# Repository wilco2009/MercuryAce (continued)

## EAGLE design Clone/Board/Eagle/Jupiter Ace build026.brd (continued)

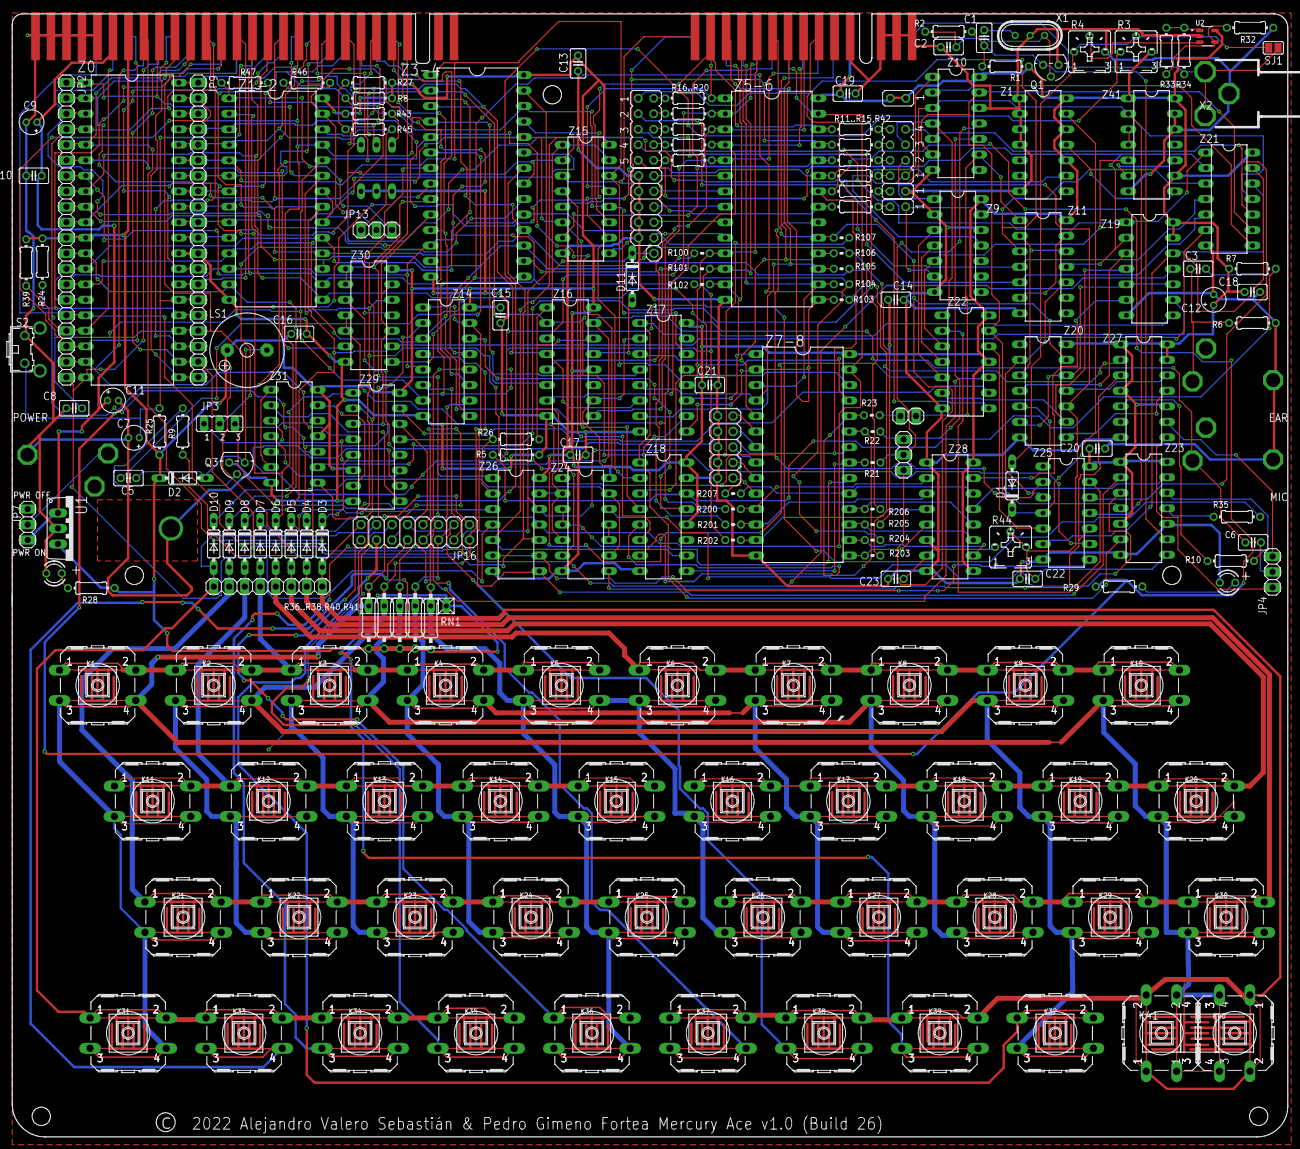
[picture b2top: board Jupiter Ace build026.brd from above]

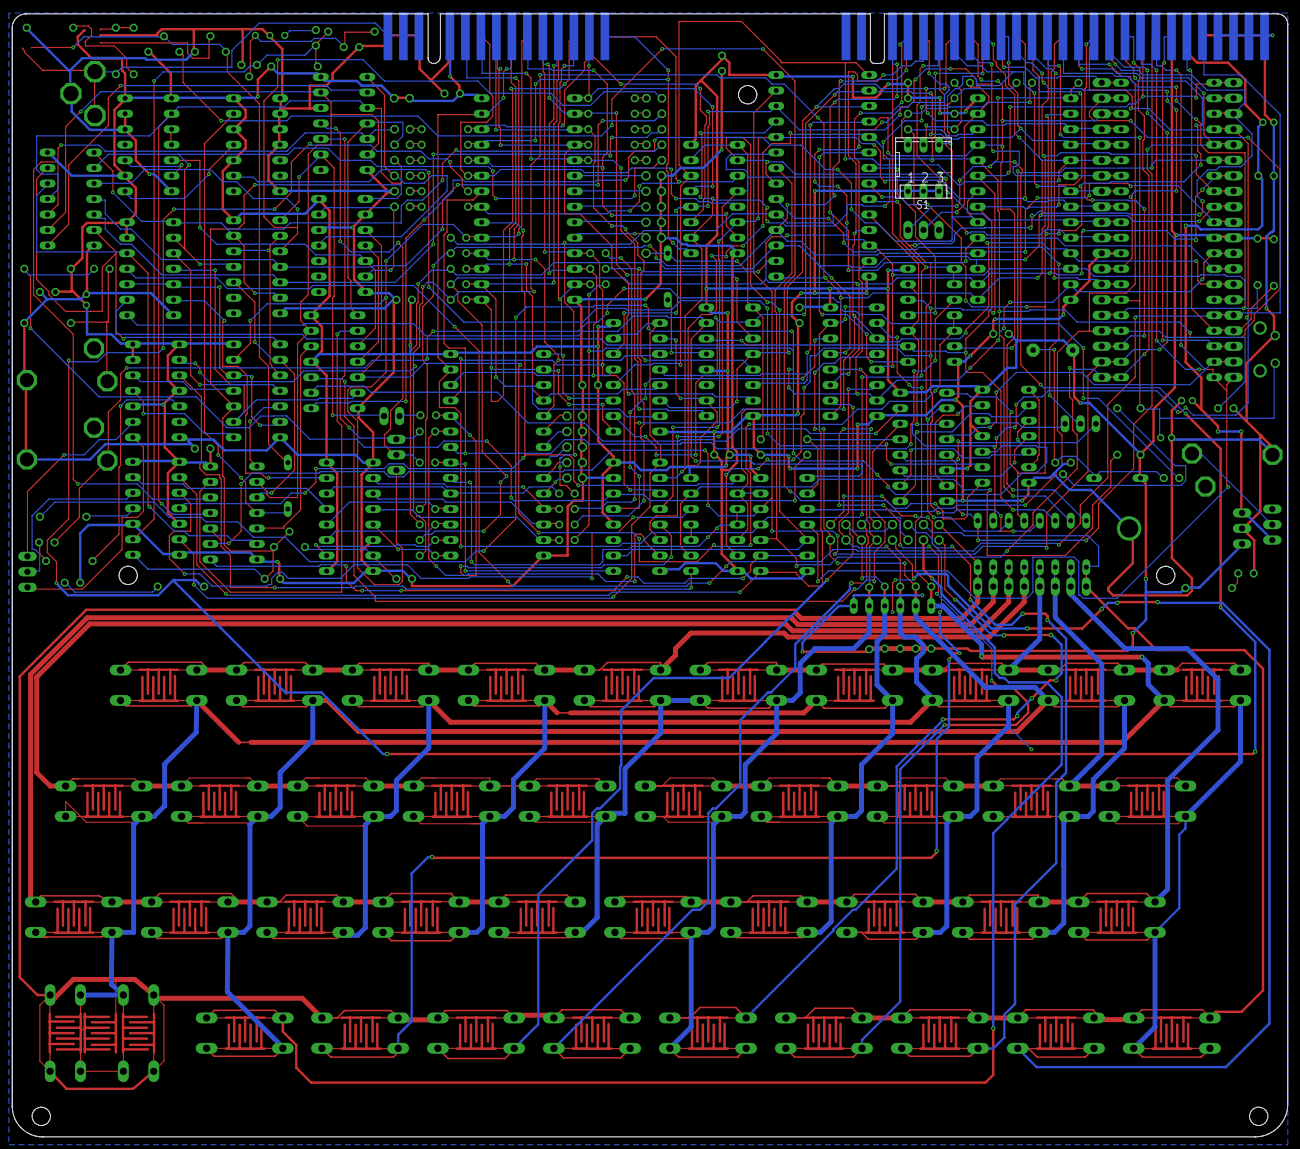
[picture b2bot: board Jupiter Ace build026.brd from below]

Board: 2 copper layers, 209.0 x 184.0 mm, 321 parts (42 on the bottom side), 211 nets.

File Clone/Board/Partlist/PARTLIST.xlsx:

Part | Value | Device | Package | Description | ONLY WITHOUT ACE81 | ONLY WITH ACE81 | ONLY WITH SJ1 OPENED
K1..K41 |  | PUSH BUTTON | B3F-40XXNOHOLE | OMRON
R35 | 300 | R-EU_0204/7 | 0204/7 | RESISTOR,
R26 | 330 | R-EU_0204/7 | 0204/7 | RESISTOR,
R28,R29 | 680 | R-EU_0204/7 | 0204/7 | RESISTOR,
R32 |  | 0204/7 | RESISTOR, | European |  |  | Y
R33 |  | 0204/7 | RESISTOR, | European |  |  | Y
R34 |  | 0204/7 | RESISTOR, | European |  |  | Y
R8,R10,R24,R27,R39,R42 | 10K | R-EU_0204/7 | 0204/7 | RESISTOR,
R5 | 12K | R-EU_0204/7 | 0204/7 | RESISTOR,
R4 | 1K | TRIM_EU-B25P | B25P | POTENTIOMETER |  |  | Y
R1,R6,R11..R23,R100..R107,R200,R207 | 1K | R-EU_0204/7 | 0204/7 | RESISTOR,
R9 | 22K | R-EU_0204/7 | 0204/7 | RESISTOR,
R7 | 33K | R-EU_0204/7 | 0204/7 | RESISTOR,
R2 | 47K | R-EU_0204/7 | 0204/7 | RESISTOR,
R3 | 500R | TRIM_EU-B25P | B25P | POTENTIOMETER
R44 | 1K | TRIM_EU-B25P | B25P | POTENTIOMETER
R30,R31 | 4k7 | R-EU_0204/7 | 0204/7 | RESISTOR, |  | Y
R36..R38,R40,R41 | 4k7 | R-EU_0204/7 | 0204/7 | RESISTOR,
R45..R47 | 4k7 | R-EU_0204/7 | 0204/7 | RESISTOR,
RN1 (instead R36,R37,R38,R40,R41) | 4K7 | RN05 | RN-6 | RESISTOR NETWORK
C4 | DO NOT INSTALL
C10,C13..C21 | 100nF | C-EU025-025X050 | C025-025X050 | CAPACITOR,
C2 | 100pF | C-EU025-025X050 | C025-025X050 | CAPACITOR,
C9 | 100uF | CPOL-EUE1.8-4 | E1,8-4 | POLARIZED
C7,C11,C12 | 1uF | CPOL-EUE1.8-4 | E1,8-4 | POLARIZED
C3 | 2.2uF | C-EU025-025X050 | C025-025X050 | CAPACITOR,
C8 | 2.2nF | C-EU025-025X050 | C025-025X050 | CAPACITOR,
C1 | 30pF | C-EU025-025X050 | C025-025X050 | CAPACITOR,
C22 | 470pF | C-EU025-025X050 | C025-025X050 | CAPACITOR,
C6 | 47nF | C-EU025-025X050 | C025-025X050 | CAPACITOR,
C5 | 47pF | C-EU025-025X050 | C025-025X050 | CAPACITOR,
C23 | 10pF | C-EU025-025X050 | C025-025X050 | CAPACITOR,
D1..D17 | 1N4148DO35-7 | 1N4148DO35-7 | DO35-7 | DIODE | Replace D12..D17 by a 0R resistor
U1 | 7805 | 7805TV | TO220V | Positive
Z1-2 | 27C512 | 27512G | DIL28-6 | MEMORY
Q1 | 2N3904 | 2N3904 | TO92 | NPN
X1 | 6.5MHz | 8M10AHC49T | HC49U | Monolithic
Z0 | Z80 | Z80CPU | DIL40 | Z80
Z1,Z27 | 74LS74N | 74LS74N | DIL14 | Dual
Z3-4,Z5-6,Z7-8 | CY62256LL-PC | SRAM | DIL28-6 | 256Kbit (32KBx8)
Z9,Z10,Z11 | 74LS393N | 74LS393N | DIL14 | Dual
Z14..Z18 | 74367N | 74367N | DIL16 | Hex
Z19,Z30,Z41 | 74LS00N | 74LS00N | DIL14 | Quad
Z20 | 74LS08N | 74LS08N | DIL14 | Quad
Z21,Z22,Z31 | 74LS11N | 74LS11N | DIL14 | Triple
Z23 | 74LS86N | 74LS86N | DIL14 | Quad
Z24,Z25 | 74LS02N | 74LS02N | DIL14 | Quad
Z26 | 74LS32N | 74LS32N | DIL14 | Quad
Z29 | 74LS138N | 74LS138N | DIL16 | 3-line
Z28 | 74LS166N | 74LS166N | DIL16 | 8-bit
Z40 | ATF16V8BP3 | ATF16V8BP3 | DIL20 | High | N | Y
LED1 | POWER | RED | LED3MM | LED
LED2 | ACE81 | BLUE | LED3MM | LED | N | Y
Q3 | BC337 | BC337 | TO92 | NPN
X2 | VIDEO CONN | AV-8.4-5 3 PINES
LS1 | PASSIVE BUZZER 16 ohm | F/QMX | F/QMX | BUZZER
U2 | MAX4390EUK | MAX4390EUK | SOT95P280X145-5N |  |  |  | Y
EAR,MIC,POWER | JACK 3.5mm | PJ302M | PJ302M | PJ302M
S2 | RESET | PUSH BUTTON 90º | B3F-31XX | OMRON
S1 | DIPSWITCH | DS02 | DS-02 | DIL/CODE

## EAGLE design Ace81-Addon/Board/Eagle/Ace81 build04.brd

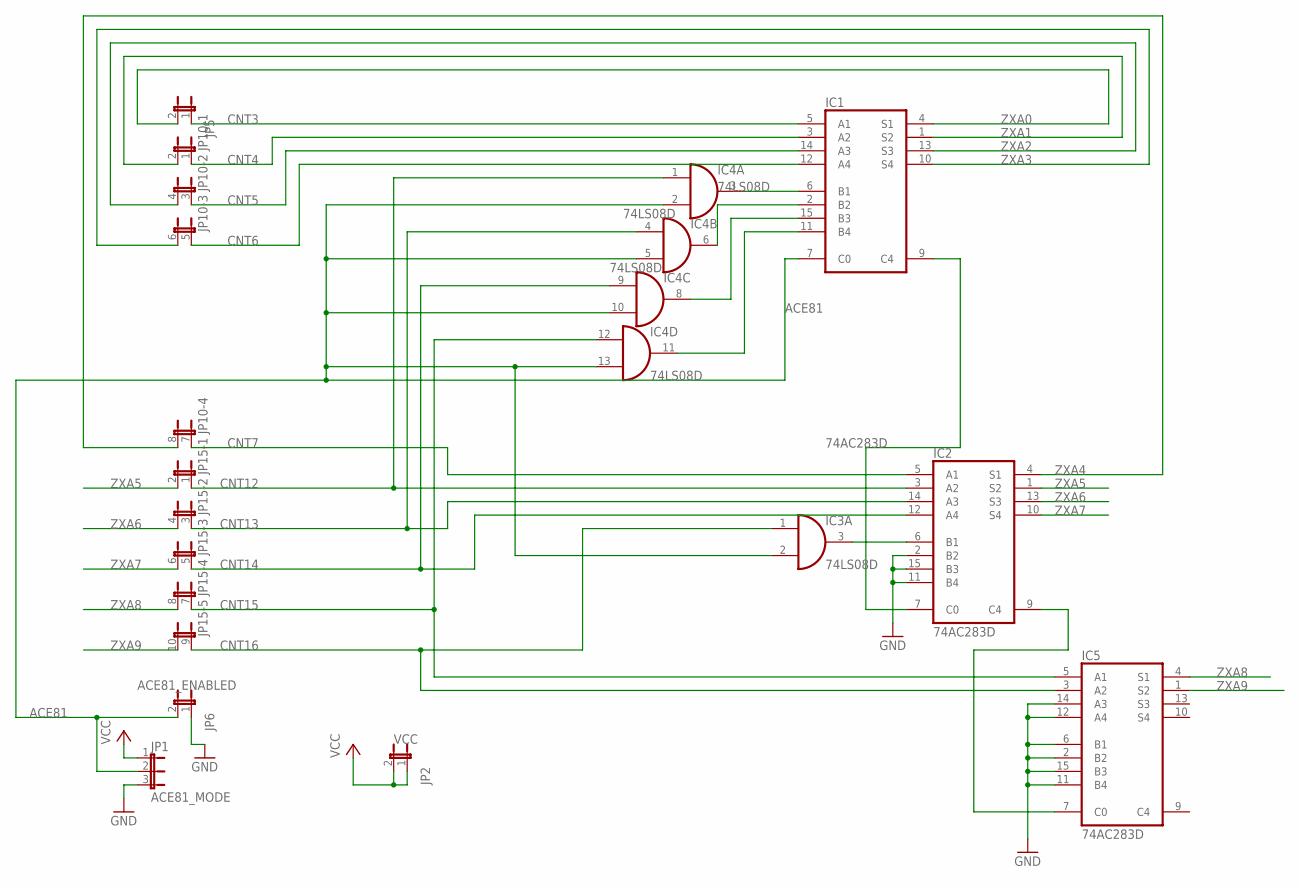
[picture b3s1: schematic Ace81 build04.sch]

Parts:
IC1, IC2, IC5: 74AC283D; SO16
IC3, IC4: 74LS08D; SO14
JP1: ACE81_MODE; JP2
JP2: VCC; JP1Q
JP5: JP1E1Q; JP1Q
JP6: ACE81_ENABLED; JP1Q
JP10: JP4QE; JP4Q
JP15: JP5QE; JP5Q

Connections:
ACE81: IC1.7 (C0), IC3.2 (I1), IC4.2 (I1), IC4.5 (I1), IC4.10 (I1), IC4.13 (I1), JP1.2, JP6.2
CNT3: IC1.5 (A1), JP5.1
CNT4: IC1.3 (A2), JP10.1
CNT5: IC1.14 (A3), JP10.3 (1)
CNT6: IC1.12 (A4), JP10.5 (1)
CNT7: IC2.5 (A1), JP10.7 (1)
CNT12: IC2.3 (A2), IC4.1 (I0), JP15.1
CNT13: IC2.14 (A3), IC4.4 (I0), JP15.3 (1)
CNT14: IC2.12 (A4), IC4.9 (I0), JP15.5 (1)
CNT15: IC4.12 (I0), IC5.5 (A1), JP15.7 (1)
CNT16: IC3.1 (I0), IC5.3 (A2), JP15.9 (1)
GND: IC1.8 (GND), IC2.2 (B2), IC2.8 (GND), IC2.11 (B4), IC2.15 (B3), IC3.7 (GND), IC4.7 (GND), IC5.2 (B2), IC5.6 (B1), IC5.8 (GND), IC5.11 (B4), IC5.12 (A4), IC5.14 (A3), IC5.15 (B3), JP1.3, JP6.1
unnamed: IC1.9 (C4), IC2.7 (C0)
unnamed: IC2.9 (C4), IC5.7 (C0)
unnamed: IC1.6 (B1), IC4.3 (O)
unnamed: IC1.2 (B2), IC4.6 (O)
unnamed: IC1.15 (B3), IC4.8 (O)
unnamed: IC1.11 (B4), IC4.11 (O)
unnamed: IC2.6 (B1), IC3.3 (O)
VCC: IC1.16 (VCC), IC2.16 (VCC), IC3.14 (VCC), IC4.14 (VCC), IC5.16 (VCC), JP1.1, JP2.1, JP2.2
ZXA0: IC1.4 (S1), JP5.2
ZXA1: IC1.1 (S2), JP10.2
ZXA2: IC1.13 (S3), JP10.4 (2)
ZXA3: IC1.10 (S4), JP10.6 (2)
ZXA4: IC2.4 (S1), JP10.8 (2)
ZXA5: IC2.1 (S2), JP15.2
ZXA6: IC2.13 (S3), JP15.4 (2)
ZXA7: IC2.10 (S4), JP15.6 (2)
ZXA8: IC5.4 (S1), JP15.8 (2)
ZXA9: IC5.1 (S2), JP15.10 (2)

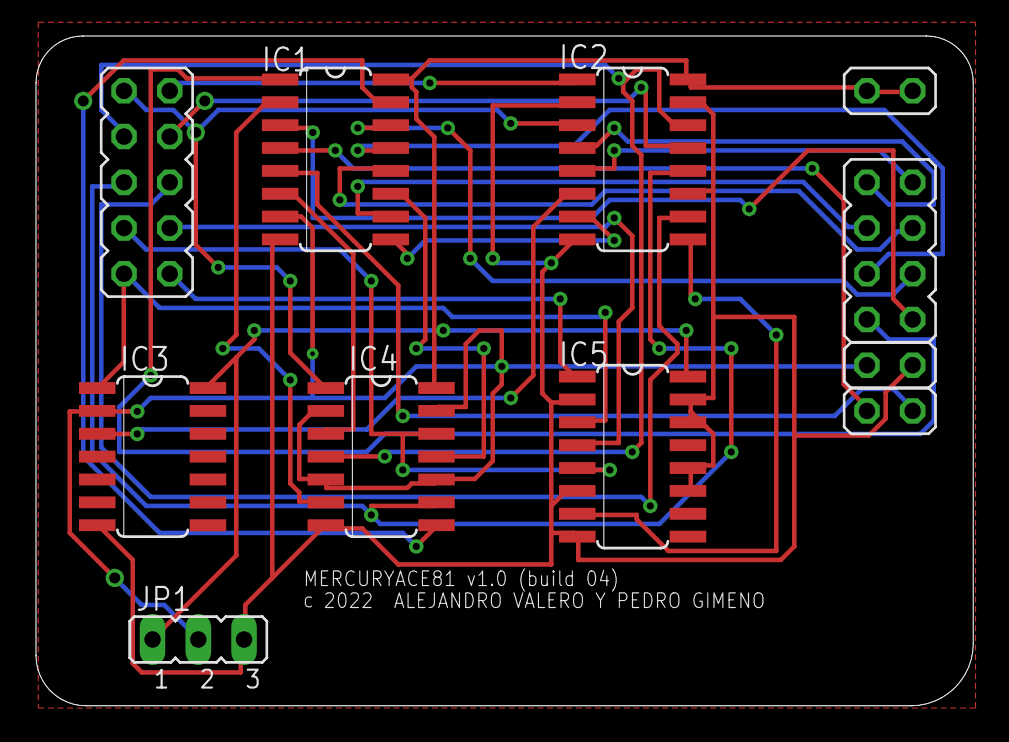
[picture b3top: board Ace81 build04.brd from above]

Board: 2 copper layers, 52.1 x 37.2 mm, 11 parts (0 on the bottom side), 30 nets.

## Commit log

2024-08-25 multilanguaje
2024-08-25 Spanish/English
2024-08-26 BUILD 024
2024-08-26 doc build024
2024-08-26 case with holes for ROMSEL
2024-08-27 circuit
2024-08-27 case
2024-08-29 roms
2024-08-30 conflicto
2024-09-03 hires-addon
2024-09-03 build 25
2024-09-03 Eliminar LEEME.bak
2024-09-03 Eliminar README.bak
2024-09-03 gerber build 25
2024-09-04 capture inv bit
2024-11-11 recover
2024-11-15 copy
